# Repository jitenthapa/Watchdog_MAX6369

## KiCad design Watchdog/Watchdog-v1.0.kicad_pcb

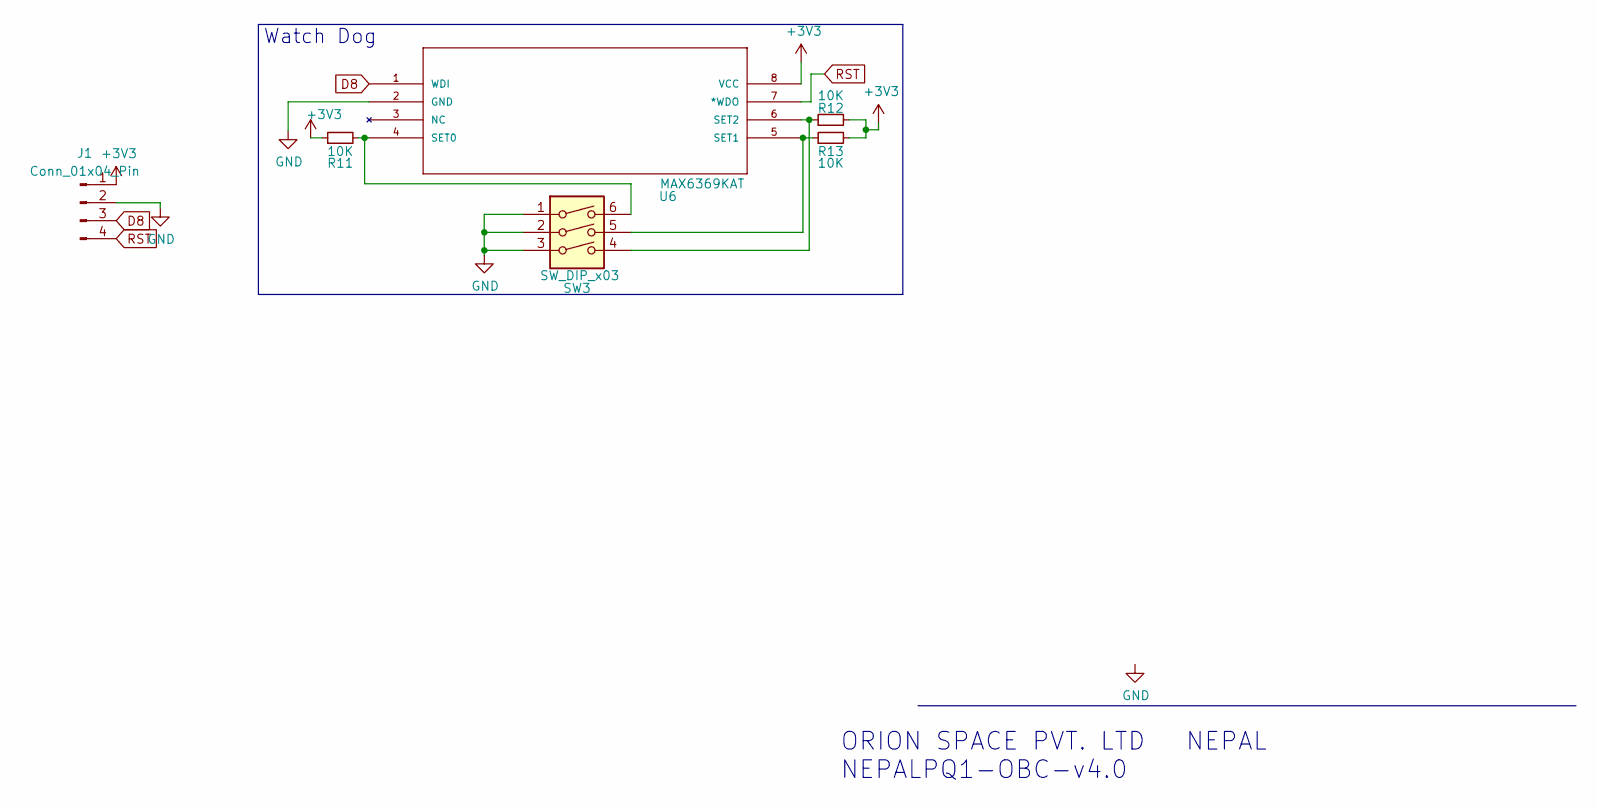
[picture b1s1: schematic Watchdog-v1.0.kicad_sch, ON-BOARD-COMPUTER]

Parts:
J1: Conn_01x04_Pin; PinHeader_1x04_P2.54mm_Vertical
R11, R12, R13: 10K; R_0805_2012Metric
SW3: SW_DIP_x03; SW_DIP_SPSTx03_Slide_9.78x9.8mm_W7.62mm_P2.54mm
U6: MAX6369KAT; 21-0078H

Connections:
+3V3: J1.1, R11.1, R12.2, R13.2, U6.8 (VCC)
D8: J1.3, U6.1 (WDI)
GND: J1.2, SW3.1, SW3.2, SW3.3, U6.2 (GND)
unnamed: R11.2, SW3.6, U6.4 (SET0)
unnamed: R13.1, SW3.5, U6.5 (SET1)
unnamed: R12.1, SW3.4, U6.6 (SET2)
RST: J1.4, U6.7 (*WDO)

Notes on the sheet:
Watch Dog
ORION SPACE PVT. LTD NEPAL NEPALPQ1-OBC-v4.0

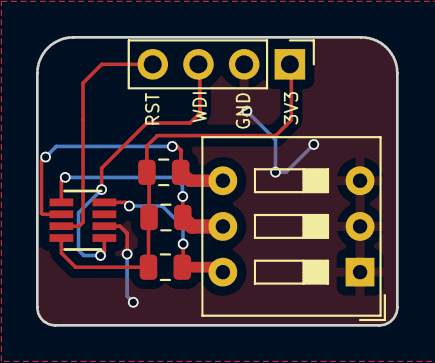
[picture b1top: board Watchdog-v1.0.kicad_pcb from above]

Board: 2 copper layers, 20.0 x 16.0 mm, 6 parts (0 on the bottom side), 7 nets.

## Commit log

2024-11-28 v1 updates
    remove switch and put jumpers
    rotate watchdog chip
